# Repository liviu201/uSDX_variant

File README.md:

For information about configuring KiCad for this project, go to [Configuring_KiCad.md](./Configuring_KiCad.md)

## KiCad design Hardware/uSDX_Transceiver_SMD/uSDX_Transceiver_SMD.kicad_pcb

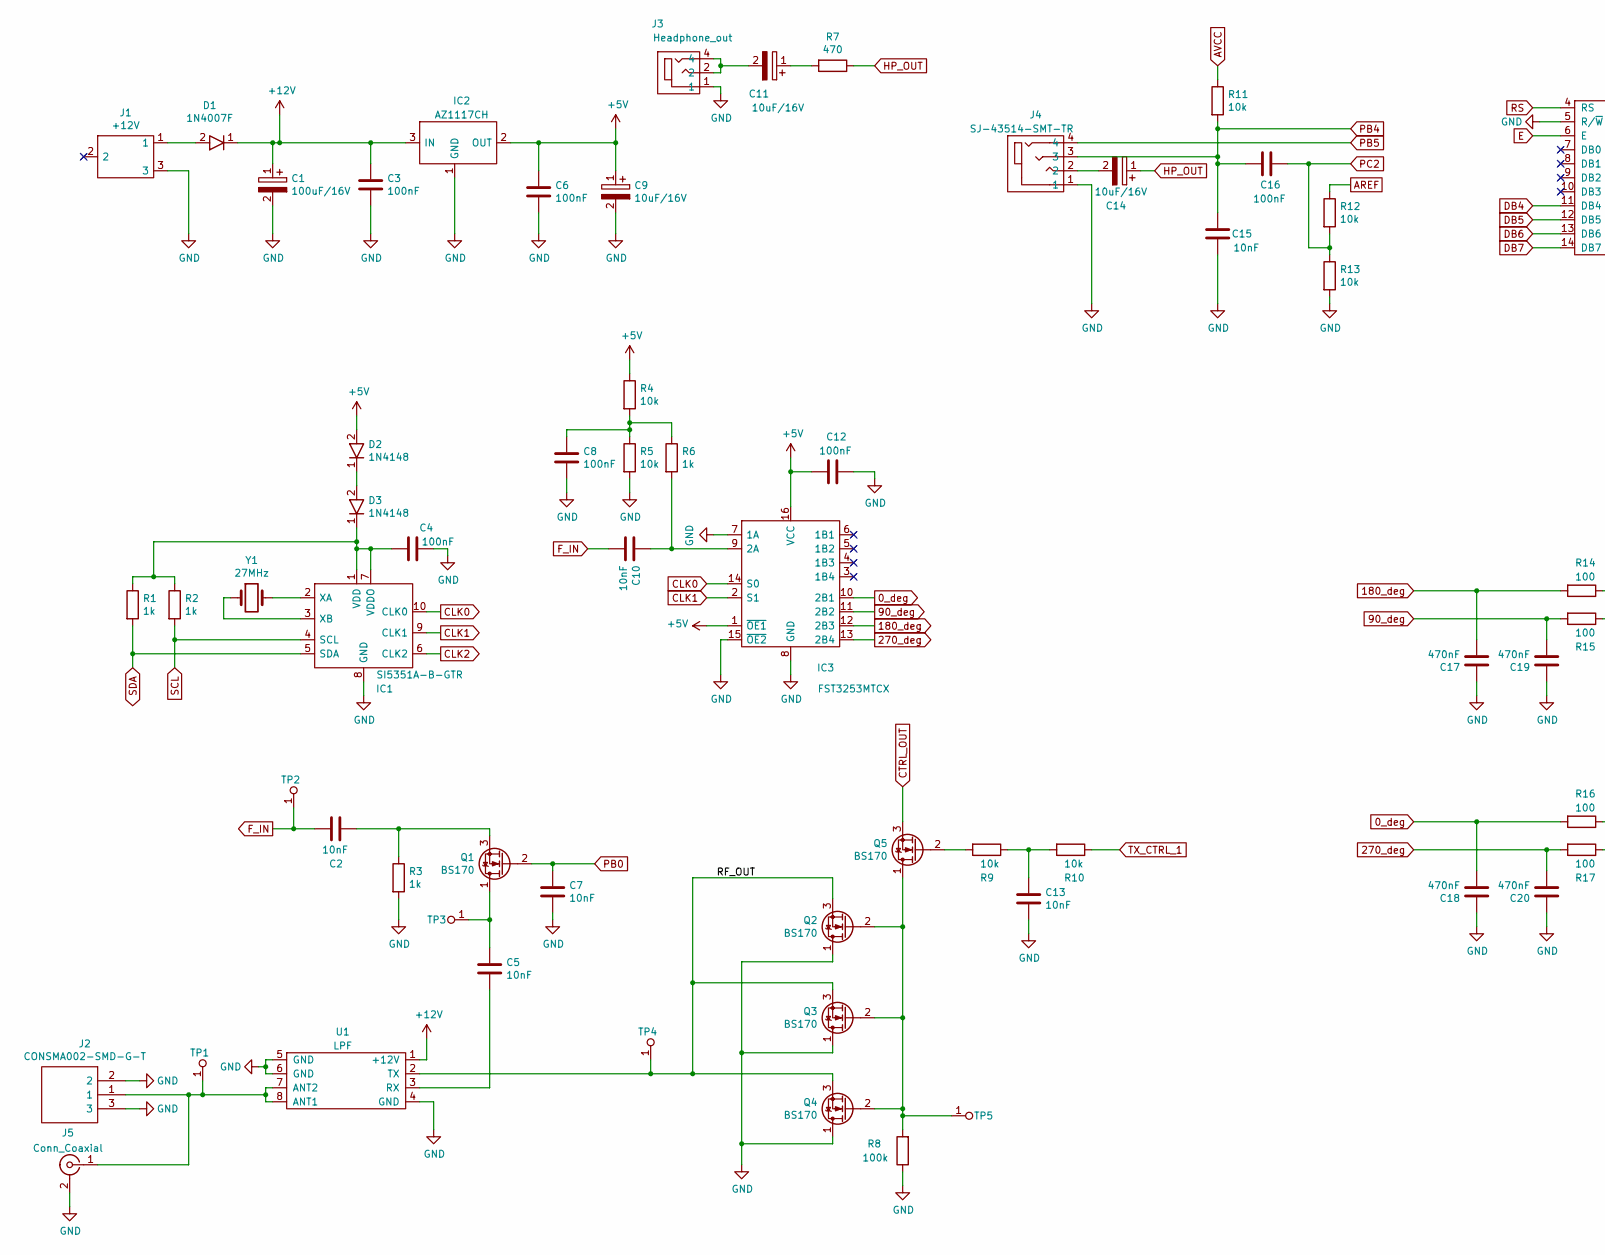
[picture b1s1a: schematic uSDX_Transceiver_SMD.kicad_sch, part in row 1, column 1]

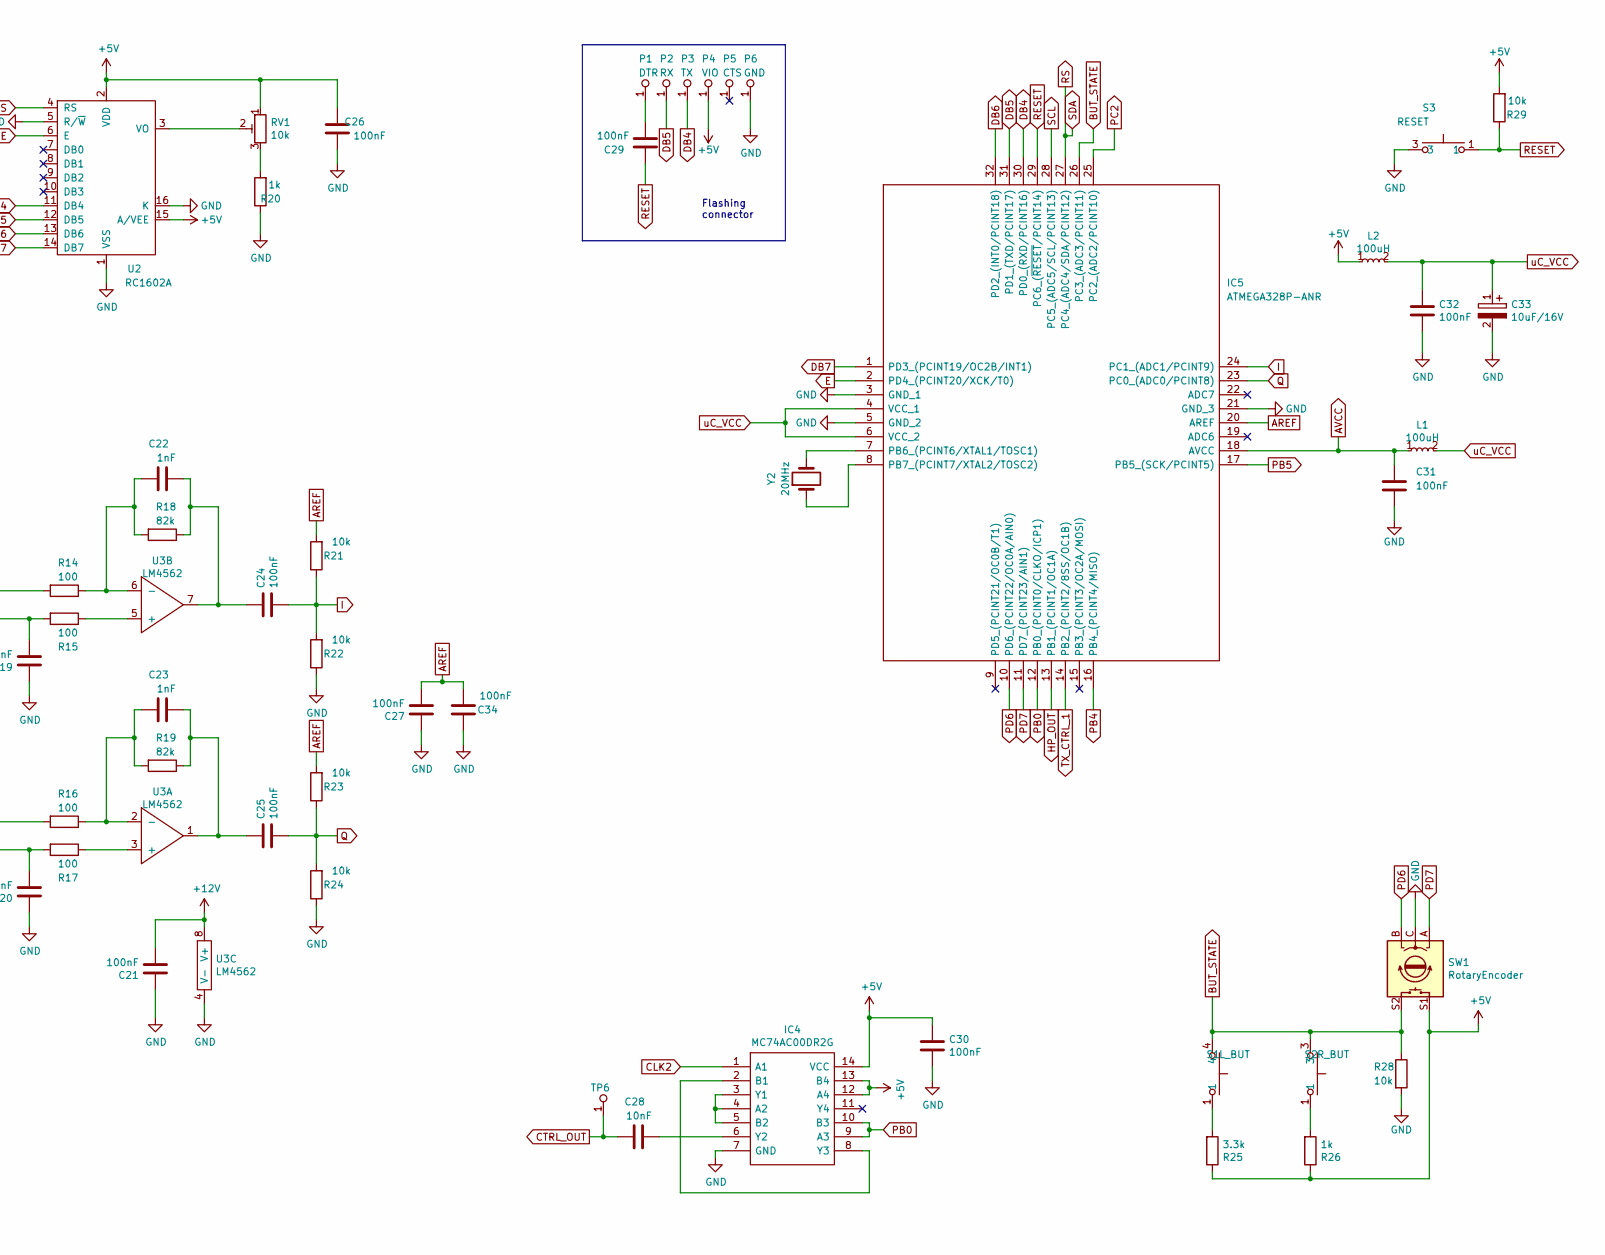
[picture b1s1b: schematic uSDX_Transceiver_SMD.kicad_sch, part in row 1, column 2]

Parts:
C1: 100uF/16V; EEE0GA101SR; Manufacturer_Part_Number EEE-FK1C101SR; Mouser Part Number 667-EEE-FK1C101SR
C2, C5, C7, C10, C13, C15, C28: 10nF; C_0805_2012Metric
C3, C4, C6, C8, C12, C16, C21, C24, C25, C26, C27, C29, C30, C31, C32, C34: 100nF; C_0805_2012Metric
C9, C11, C14, C33: 10uF/16V; CAPAE430X470N; Manufacturer_Part_Number UCQ1C100MCL1GB; Mouser Part Number 647-UCQ1C100MCL1GB
C17, C18, C19, C20: 470nF; C_0805_2012Metric
C22, C23: 1nF; C_0805_2012Metric
D1: 1N4007F; SODFL4626X110N; Manufacturer_Part_Number 1N4007F
D2, D3: 1N4148; SOD3816X135N; Manufacturer_Part_Number 1N4148W_R2_00001; Mouser Part Number 241-1N4148W_R2_00001
IC1: SI5351A-B-GTR; SOP50P490X110-10N; Manufacturer_Part_Number SI5351A-B-GTR; Mouser Part Number 634-SI5351A-B-GTR
IC2: AZ1117CH; SOT230P700X180-4N; Manufacturer_Part_Number LM1117MPX-50NOPB; Mouser Part Number 863-LM1117MPX-50NOPB
IC3: FST3253MTCX; SOP65P640X110-16N; Manufacturer_Part_Number FST3253MTCX; Mouser Part Number 512-FST3253MTCX
IC4: MC74AC00DR2G; SOIC127P600X175-14N; Manufacturer_Part_Number MC74AC00DR2G; Mouser Part Number 863-MC74AC00DR2G
IC5: ATMEGA328P-ANR; QFP80P900X900X120-32N; Manufacturer_Part_Number ATMEGA328P-ANR; Mouser Part Number 556-ATMEGA328P-ANR
J1: +12V; RASM722BKZ; Manufacturer_Part_Number 16PJ200
J2: CONSMA002-SMD-G-T; CONSMA002SMDGT; Manufacturer_Part_Number CONSMA002-SMD-G-T; Mouser Part Number 712-CONSMA002-SMD-GT
J3: Headphone_out; STX31503C1; Manufacturer_Part_Number STX-3150-3C-1; Mouser Part Number 806-STX-3150-3C-1
J4: SJ-43514-SMT-TR; SJ43514SMTTR; Manufacturer_Part_Number SJ-43514-SMT-TR; Mouser Part Number 490-SJ-43514-SMT-TR
J5: Conn_Coaxial; BNC_1-1634613-0
L1: 100uH; VLS3010CX-101M-1
L2: 100uH; MSS6122-104MLC
P1: DTR; pin_angled
P2: RX; pin_angled
P3: TX; pin_angled
P4: VIO; pin_angled
P5: CTS; pin_angled
P6: GND; pin_angled
Q1, Q2, Q3, Q4, Q5: BS170; TO-92
R1, R2, R3, R6, R20, R26: 1k; R_0805_2012Metric
R4, R5, R9, R10, R11, R12, R13, R21, R22, R23, R24, R28, R29: 10k; R_0805_2012Metric
R7: 470; R_0805_2012Metric
R8: 100k; R_0805_2012Metric
R14, R15, R16, R17: 100; R_0805_2012Metric
R18, R19: 82k; R_0805_2012Metric
R25: 3.3k; R_0805_2012Metric
RV1: 10k; Potentiometer_Vishay_TS53YJ_Vertical
S1: L_BUT; PTS125SM122LFS; Manufacturer_Part_Number PTS125SM122LFS; Mouser Part Number 611-PTS125SM12LFS
S2: R_BUT; PTS125SM122LFS; Manufacturer_Part_Number PTS125SM122LFS; Mouser Part Number 611-PTS125SM12LFS
S3: RESET; pushbutton; Manufacturer_Part_Number PTS125SM122LFS; Mouser Part Number 611-PTS125SM12LFS
SW1: RotaryEncoder; PEC11H-4220F-S0024
TP1, TP2, TP3, TP4, TP5, TP6: testpoint
U1: LPF; BPF_board
U2: RC1602A; RC1602BBIWESX
U3: LM4562; SOIC127P600X175-8N
Y1: 27MHz; XRCGB27M000F2P01R0
Y2: 20MHz; 830108207209

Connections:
0_deg: C18.2, IC3.10 (2B1), R16.2
90_deg: C19.2, IC3.11 (2B2), R15.2
180_deg: C17.2, IC3.12 (2B3), R14.2
270_deg: C20.2, IC3.13 (2B4), R17.2
+5V: C6.1, C9.1, C12.2, C26.2, C30.1, D2.2, IC2.2 (OUT), IC3.1 (~OE1), IC3.16 (VCC), IC4.12 (A4), IC4.13 (B4), IC4.14 (VCC), L2.1, P4.1, R4.1, R25.1, R26.1, R29.2, RV1.1, SW1.S1, U2.2 (VDD), U2.15 (A/VEE)
+12V: C1.1, C3.1, C21.2, D1.1, IC2.3 (IN), U1.1 (+12V), U3.8 (V+)
/RF_OUT: Q2.3 (S), Q3.3 (S), Q4.3 (S), TP4.1, U1.2 (TX)
AREF: C27.2, C34.2, IC5.20 (AREF), R12.1, R21.2, R23.2
AVCC: C31.1, IC5.18 (AVCC), L1.1, R11.1
BUT_STATE: IC5.26 (PC3_(ADC3/PCINT11)), R28.1, S1.4, S2.3, SW1.S2
CLK0: IC1.10 (CLK0), IC3.14 (S0)
CLK1: IC1.9 (CLK1), IC3.2 (S1)
CLK2: IC1.6 (CLK2), IC4.1 (A1)
CTRL_OUT: C28.1, Q5.3 (S), TP6.1
DB4: IC5.30 (PD0_(RXD/PCINT16)), P3.1, U2.11 (DB4)
DB5: IC5.31 (PD1_(TXD/PCINT17)), P2.1, U2.12 (DB5)
DB6: IC5.32 (PD2_(INT0/PCINT18)), U2.13 (DB6)
DB7: IC5.1 (PD3_(PCINT19/OC2B/INT1)), U2.14 (DB7)
E: IC5.2 (PD4_(PCINT20/XCK/T0)), U2.6 (E)
F_IN: C2.2, C10.2, TP2.1
GND: C1.2, C3.2, C4.2, C6.2, C7.2, C8.2, C9.2, C12.1, C13.2, C15.1, C17.1, C18.1, C19.1, C20.1, C21.1, C26.1, C27.1, C30.2, C31.2, C32.2, C33.2, C34.1, IC1.8 (GND), IC2.1 (GND), IC3.7 (1A), IC3.8 (GND), IC3.15 (~OE2), IC4.7 (GND), IC5.3 (GND_1), IC5.5 (GND_2), IC5.21 (GND_3), J1.3, J2.2, J2.3, J3.1, J4.1, J5.2 (Ext), P6.1, Q2.1 (D), Q3.1 (D), Q4.1 (D), R3.2, R5.2, R8.1, R13.2, R20.1, R22.1, R24.1, R28.2, S3.3, SW1.C, U1.4 (GND), U1.5 (GND), U1.6 (GND), U2.1 (VSS), U2.5 (R/~W), U2.16 (K), U3.4 (V-)
HP_OUT: C14.1, IC5.13 (PB1_(PCINT1/OC1A)), R7.1
I: C24.2, IC5.24 (PC1_(ADC1/PCINT9)), R21.1, R22.2
unnamed: C2.1, Q1.3 (S), R3.1
unnamed: C4.1, D3.1, IC1.1 (VDD), IC1.7 (VDDO), R1.1, R2.1
unnamed: C5.1, Q1.1 (D), TP3.1
unnamed: C5.2, U1.3 (RX)
unnamed: C8.1, R4.2, R5.1, R6.1
unnamed: C10.1, IC3.9 (2A), R6.2
unnamed: C11.1, R7.2
unnamed: C11.2, J3.2, J3.4
unnamed: C13.1, R9.1, R10.2
unnamed: C14.2, J4.2
unnamed: C22.1, R14.1, R18.2, U3.6 (-)
unnamed: C22.2, C24.1, R18.1, U3.7
unnamed: C23.1, R16.1, R19.2, U3.2 (-)
unnamed: C23.2, C25.1, R19.1, U3.1
unnamed: C28.2, IC4.6 (Y2)
unnamed: C29.1, P1.1
unnamed: D1.2, J1.1
unnamed: D2.1, D3.2
unnamed: IC1.2 (XA), Y1.3
unnamed: IC1.3 (XB), Y1.1
unnamed: IC4.2 (B1), IC4.8 (Y3)
unnamed: IC4.3 (Y1), IC4.4 (A2), IC4.5 (B2)
unnamed: IC5.7 (PB6_(PCINT6/XTAL1/TOSC1)), Y2.3
unnamed: IC5.8 (PB7_(PCINT7/XTAL2/TOSC2)), Y2.1
unnamed: J2.1, J5.1 (In), TP1.1, U1.7 (ANT2), U1.8 (ANT1)
unnamed: Q2.2 (G), Q3.2 (G), Q4.2 (G), Q5.1 (D), R8.2, TP5.1
unnamed: Q5.2 (G), R9.2
unnamed: R15.1, U3.5 (+)
unnamed: R17.1, U3.3 (+)
unnamed: R20.2, RV1.3
unnamed: R25.2, S1.1
unnamed: R26.2, S2.1
unnamed: RV1.2, U2.3 (VO)
PB0: C7.1, IC4.9 (A3), IC4.10 (B3), IC5.12 (PB0_(PCINT0/CLKO/ICP1)), Q1.2 (G)
PB4: C15.2, C16.2, IC5.16 (PB4_(PCINT4/MISO)), J4.3, R11.2
PB5: IC5.17 (PB5_(SCK/PCINT5)), J4.4
PC2: C16.1, IC5.25 (PC2_(ADC2/PCINT10)), R12.2, R13.1
PD6: IC5.10 (PD6_(PCINT22/OC0A/AIN0)), SW1.B
PD7: IC5.11 (PD7_(PCINT23/AIN1)), SW1.A
Q: C25.2, IC5.23 (PC0_(ADC0/PCINT8)), R23.1, R24.2
RESET: C29.2, IC5.29 (PC6_(~RESET/PCINT14)), R29.1, S3.1
RS: IC1.5 (SDA), IC5.27 (PC4_(ADC4/SDA/PCINT12)), R1.2, U2.4 (RS)
SCL: IC1.4 (SCL), IC5.28 (PC5_(ADC5/SCL/PCINT13)), R2.2
TX_CTRL_1: IC5.14 (PB2_(PCINT2/8SS/OC1B)), R10.1
uC_VCC: C32.1, C33.1, IC5.4 (VCC_1), IC5.6 (VCC_2), L1.2, L2.2

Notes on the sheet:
Flashing connector

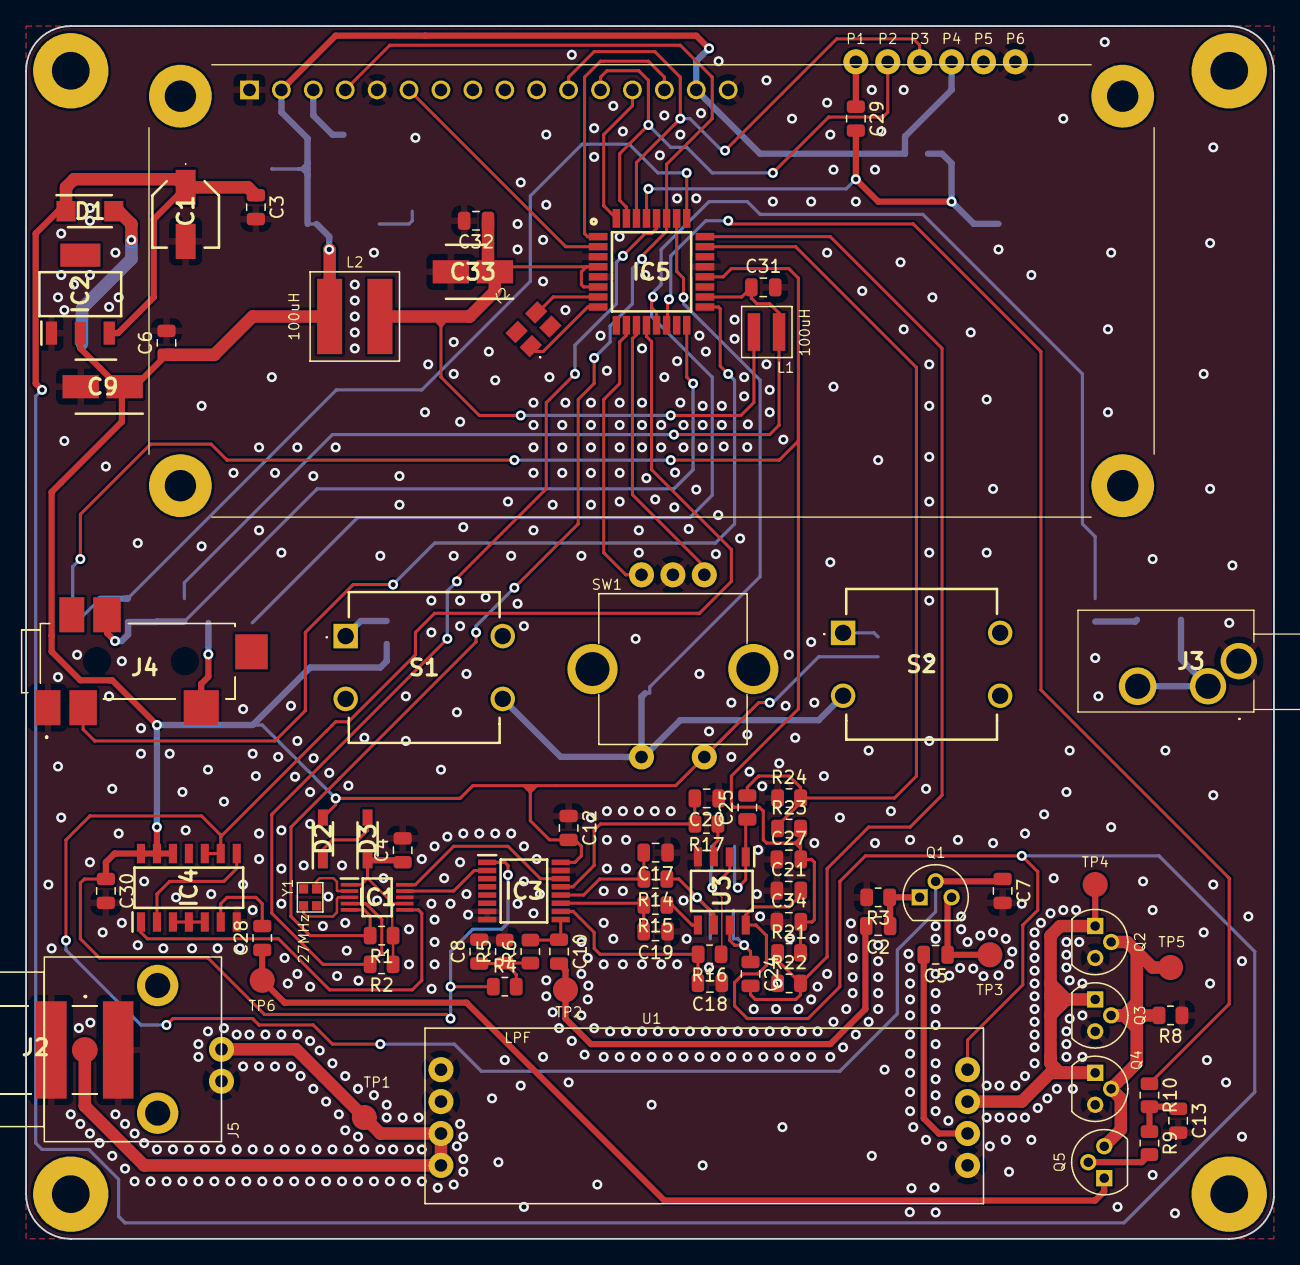
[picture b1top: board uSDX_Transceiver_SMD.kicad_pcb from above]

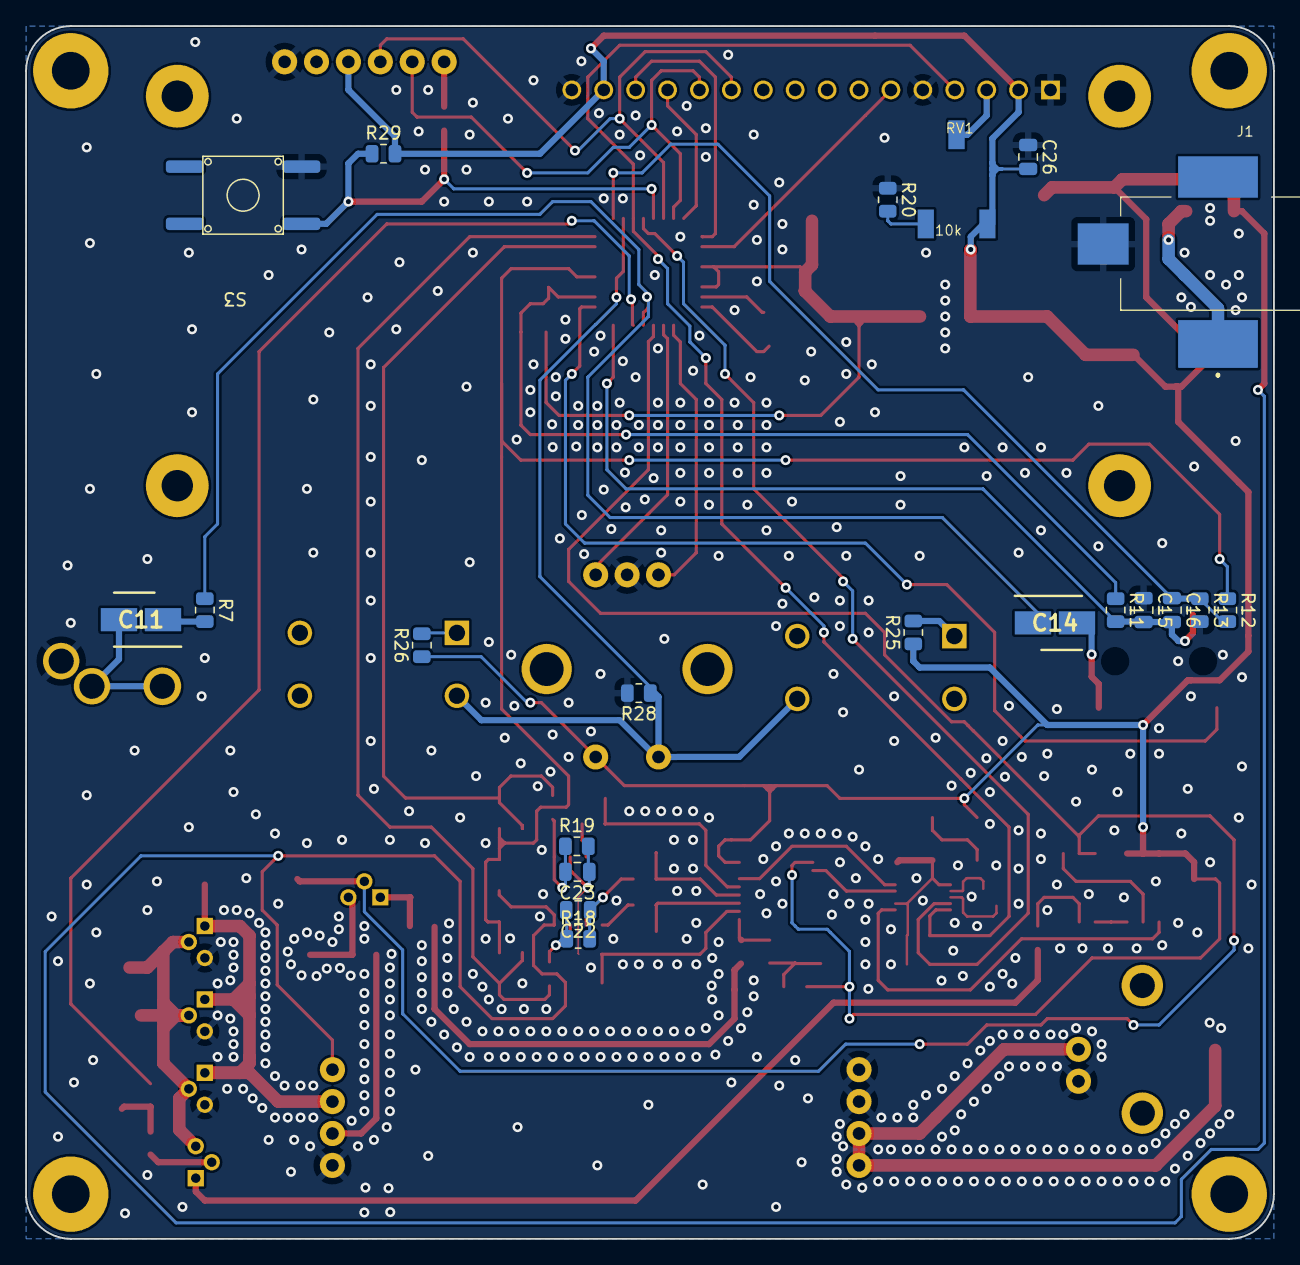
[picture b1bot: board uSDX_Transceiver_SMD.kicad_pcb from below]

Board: 2 copper layers, 99.3 x 96.5 mm, 108 parts (21 on the bottom side), 68 nets.

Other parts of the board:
 : MountingHole_3mm_Pad
 #2,  #3,  #4: MountingHole_3mm_Pad

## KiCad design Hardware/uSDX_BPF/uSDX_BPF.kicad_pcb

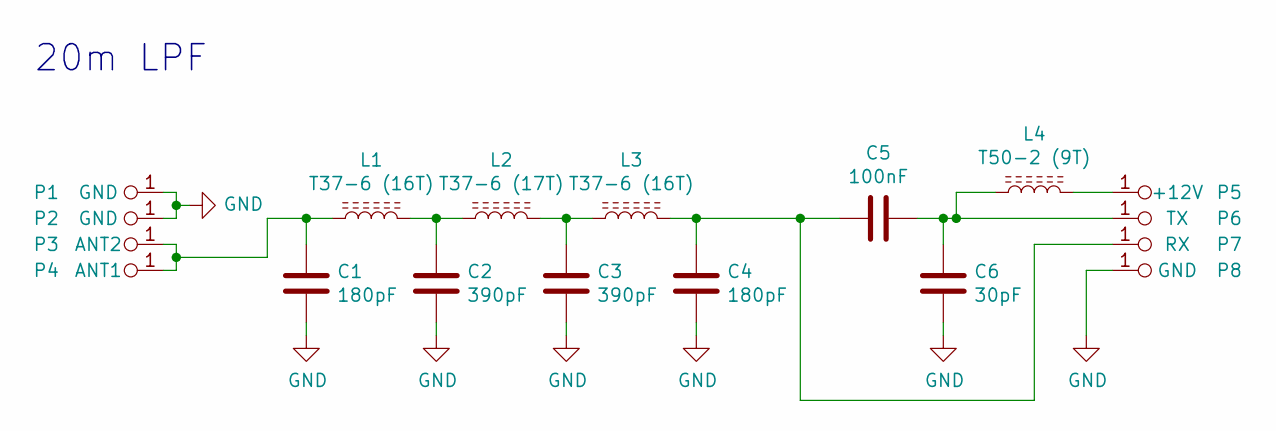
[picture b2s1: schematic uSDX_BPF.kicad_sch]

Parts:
C1, C4: 180pF; C_Disc_D3.0mm_W1.6mm_P2.50mm
C2, C3: 390pF; C_Disc_D3.0mm_W1.6mm_P2.50mm
C5: 100nF; C_Disc_D3.0mm_W1.6mm_P2.50mm
C6: 30pF; C_Disc_D3.0mm_W1.6mm_P2.50mm
L1, L3: T37-6 (16T); L_Toroid_Vertical_L10.0mm_W5.0mm_P5.08mm
L2: T37-6 (17T); L_Toroid_Vertical_L10.0mm_W5.0mm_P5.08mm
L4: T50-2 (9T); L_Toroid_Vertical_L10.0mm_W5.0mm_P5.08mm
P1, P2, P8: GND; pin
P3: ANT2; pin
P4: ANT1; pin
P5: +12V; pin
P6: TX; pin
P7: RX; pin

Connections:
GND: C1.2, C2.2, C3.2, C4.2, C6.2, P1.1, P2.1, P8.1
unnamed: C1.1, L1.1, P3.1, P4.1
unnamed: C2.1, L1.2, L2.1
unnamed: C3.1, L2.2, L3.1
unnamed: C4.1, C5.2, L3.2, P7.1
unnamed: C5.1, C6.1, L4.1, P6.1
unnamed: L4.2, P5.1

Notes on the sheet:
20m LPF

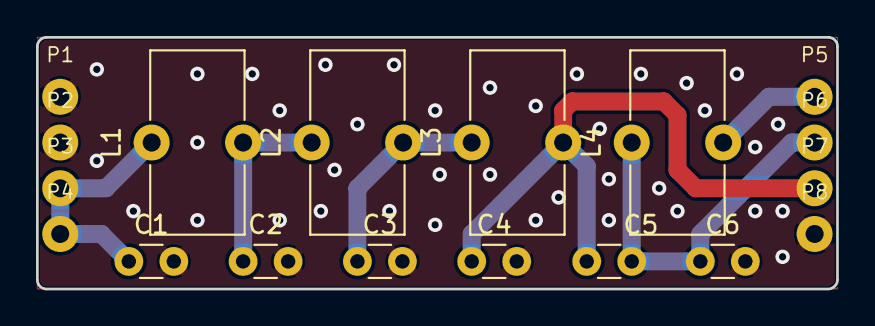
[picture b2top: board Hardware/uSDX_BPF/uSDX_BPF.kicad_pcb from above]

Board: 2 copper layers, 44.5 x 14.0 mm, 18 parts (0 on the bottom side), 7 nets.

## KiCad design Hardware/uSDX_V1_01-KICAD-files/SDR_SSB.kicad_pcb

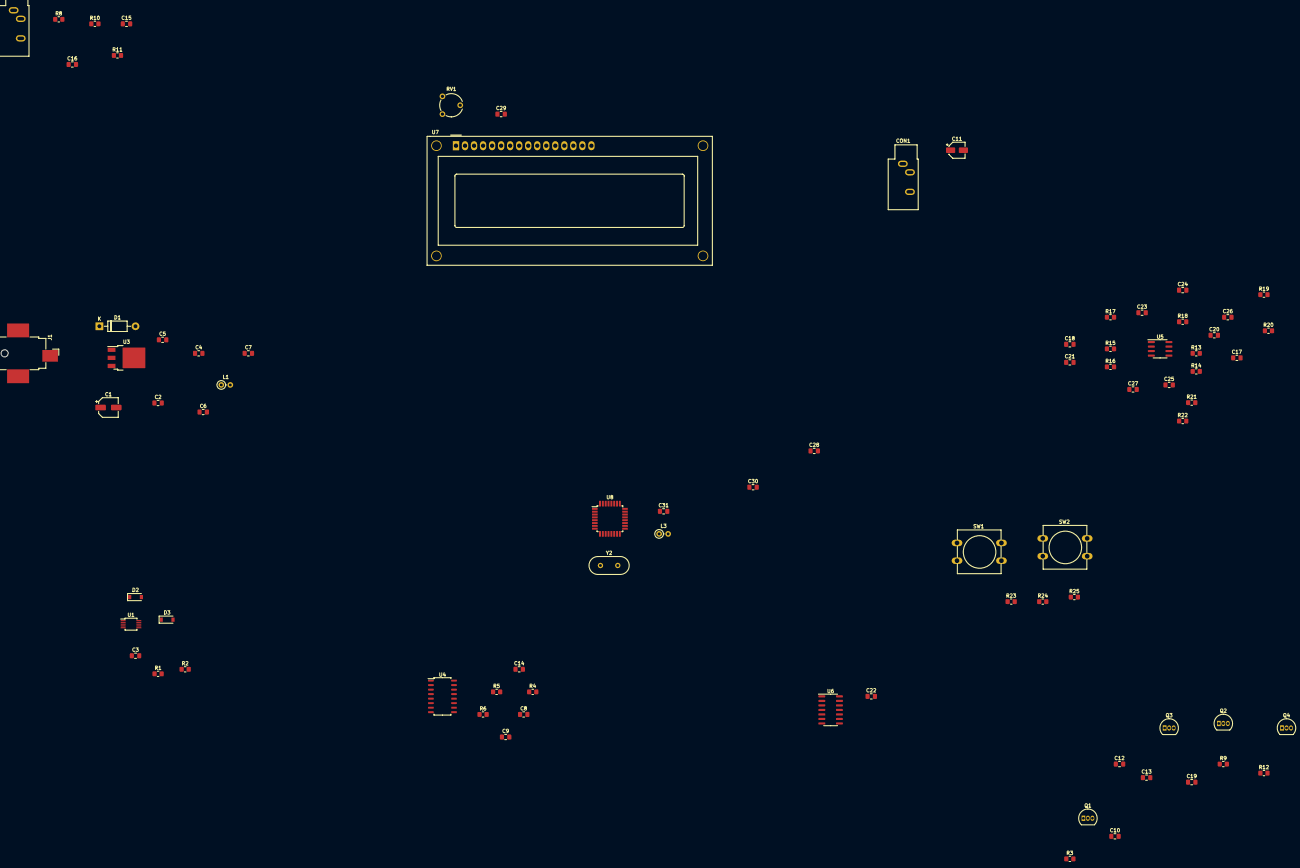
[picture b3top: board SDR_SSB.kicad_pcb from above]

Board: 2 copper layers, 79 parts (1 on the bottom side), 53 nets, no tracks yet.

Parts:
C1: 100u/16V; CP_Elec_5x5.8
C2, C3, C4, C6, C8, C12, C14, C16, C22, C25, C26, C27, C28, C29, C31: 100nF; C_0805_2012Metric_Pad1.18x1.45mm_HandSolder
C5, C7: 10uF; C_0805_2012Metric_Pad1.18x1.45mm_HandSolder
C9, C10, C15, C19, C30: 10nF; C_0805_2012Metric_Pad1.18x1.45mm_HandSolder
C11: 10uF/16V; CP_Elec_4x4.5
C13: 33pF; C_0805_2012Metric_Pad1.18x1.45mm_HandSolder
C17, C18, C20, C21: 470nF; C_0805_2012Metric_Pad1.18x1.45mm_HandSolder
C23, C24: 1nF; C_0805_2012Metric_Pad1.18x1.45mm_HandSolder
CON1: HEADPHONE; Jack_3.5mm_CUI_SJ1-3533NG_Horizontal
CON2: MIC/PTT; Jack_3.5mm_CUI_SJ1-3533NG_Horizontal
D1: 1N4007; D_DO-41_SOD81_P10.16mm_Horizontal
D2, D3: 1N4148W; D_SOD-123
J1: DC 12V; BarrelJack_CUI_PJ-036AH-SMT_Horizontal
L1, L3: 100uH; L_Axial_L5.3mm_D2.2mm_P2.54mm_Vertical_Vishay_IM-1
Q1, Q2, Q3, Q4: BS170; TO-92_Inline
R1, R2, R3, R6, R24: 1k; R_0805_2012Metric_Pad1.20x1.40mm_HandSolder
R4, R5, R8, R9, R10, R11, R12, R19, R20, R21, R22, R25: 10k; R_0805_2012Metric_Pad1.20x1.40mm_HandSolder
R7: 470; R_0805_2012Metric_Pad1.20x1.40mm_HandSolder
R13, R14, R15, R16: 100; R_0805_2012Metric_Pad1.20x1.40mm_HandSolder
R17, R18: 82k; R_0805_2012Metric_Pad1.20x1.40mm_HandSolder
R23: 3.3k; R_0805_2012Metric_Pad1.20x1.40mm_HandSolder
RV1: 10k; Potentiometer_Piher_PT-6-V_Vertical
SW1: L_Button; SW_PUSH-12mm
SW2: R_Button; SW_PUSH-12mm
U1: Si5351A-B-GT; MSOP-10_3x3mm_P0.5mm
U3: L7805CV; TO-252-3_TabPin4
U4: FST3253; SOIC-16_4.55x10.3mm_P1.27mm
U5: LM4562; SOIC-8_3.9x4.9mm_P1.27mm
U6: 74ACT00; SOIC-14_3.9x8.7mm_P1.27mm
U7: RC1602A; WC1602A
U8: ATMEGA328-PU; TQFP-32_7x7mm_P0.8mm
Y2: 20 Mhz; Crystal_HC49-U_Vertical

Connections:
0_deg: C18.1, R15.1, U4.10
90_deg: C17.2, R14.1, U4.11
180_deg: C20.2, R13.1, U4.12
270_deg: C21.1, R16.1, U4.13
+5V: C6.1, C7.1, C14.1, C22.1, C29.1, D2.2, L1.2, L3.1, R4.1, R23.2, R24.2, RV1.1, U4.1, U4.16, U6.12, U6.13, U6.14, U7.2, U7.15, U8.7
+12V: C1.1, C2.1, C25.1, D1.2, U3.1, U5.8
AREF: C28.2, R10.1, R19.2, R21.2, U8.21
AVCC: C31.1, L3.2, R8.1, U8.20
BUT_STATE: R25.1, SW1.1, SW2.1, U8.26
CLK_0: U1.10, U4.14
CLK_1: U1.9, U4.2
CLK_2: U1.6, U6.1
CTRL_OUT: C30.1, Q2.2, Q3.2, Q4.2, R9.2
DB4: U7.11, U8.2
DB5: U7.12, U8.3
DB6: U7.13, U8.4
DB7: U7.14, U8.5
E: U7.6, U8.6
F_IN: C9.2, Q1.3, R3.1
GNDPWR: C1.2, C2.2, C3.1, C4.2, C5.2, C6.2, C7.2, C8.2, C10.1, C13.2, C14.2, C15.2, C17.1, C18.2, C19.2, C20.1, C21.2, C22.2, C25.2, C28.1, C29.2, C31.2, J1.2, Q2.3, Q3.3, Q4.3, R3.2, R5.2, R11.2, R20.1, R22.1, R25.2, RV1.3, U1.8, U3.2, U4.7, U4.8, U4.15, U5.4, U6.7, U7.1, U7.5, U7.16, U8.8, U8.22
HP_OUT: R7.1, U8.15
I: C26.2, R19.1, R20.2, U8.23
unnamed: C3.2, D3.1, R1.1, R2.1, U1.1, U1.7
unnamed: C4.1, C5.1, L1.1, U3.3
unnamed: C8.1, R4.2, R5.1, R6.1
unnamed: C9.1, R6.2, U4.9
unnamed: C11.1, R7.2
unnamed: C12.1, C13.1, Q2.1, Q3.1, Q4.1
unnamed: C19.1, R9.1, R12.2
unnamed: C23.1, R15.2, R17.1, U5.2
unnamed: C23.2, C27.1, R17.2, U5.1
unnamed: C24.1, R13.2, R18.1, U5.6
unnamed: C24.2, C26.1, R18.2, U5.7
unnamed: C30.2, U6.6
unnamed: D1.1, J1.1
unnamed: D2.1, D3.2
unnamed: R14.2, U5.5
unnamed: R16.2, U5.3
unnamed: R23.1, SW1.2
unnamed: R24.1, SW2.2
unnamed: RV1.2, U7.3
unnamed: U6.2, U6.8
unnamed: U6.3, U6.4, U6.5
unnamed: U8.9, Y2.1
unnamed: U8.10, Y2.2
PB0: C10.2, Q1.2, U6.9, U6.10, U8.14
PB4: C15.1, C16.1, R8.2, U8.18
PC2: C16.2, R10.2, R11.1, U8.25
Q: C27.2, R21.1, R22.2, U8.24
RF_SIGNAL: C12.2, Q1.1
RS: R1.2, U1.5, U7.4, U8.27
SCL: R2.2, U1.4, U8.28
TX_CTRL_1: R12.1, U8.16

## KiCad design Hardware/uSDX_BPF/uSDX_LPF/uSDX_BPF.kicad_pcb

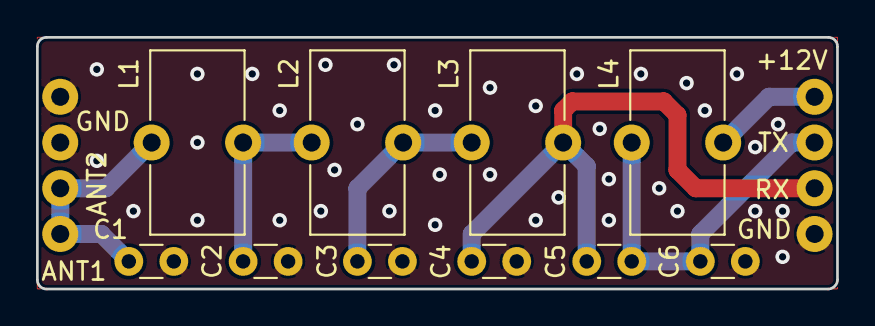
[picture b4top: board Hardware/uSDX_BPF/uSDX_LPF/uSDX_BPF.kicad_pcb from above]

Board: 2 copper layers, 44.5 x 14.0 mm, 18 parts (0 on the bottom side), 7 nets.

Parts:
 : pin
+12V: pin
ANT1, ANT2: pin
C1: 180pF; C_Disc_D3.0mm_W1.6mm_P2.50mm
C2: 390pF; C_Disc_D3.0mm_W1.6mm_P2.50mm
C3, C4, C5, C6: C_Disc_D3.0mm_W1.6mm_P2.50mm
GND: pin
GND#2: pin
L1, L3: T37-6 (16T); L_Toroid_Vertical_L10.0mm_W5.0mm_P5.08mm
L2: T37-6 (17T); L_Toroid_Vertical_L10.0mm_W5.0mm_P5.08mm
L4: L_Toroid_Vertical_L10.0mm_W5.0mm_P5.08mm
RX: pin
TX: TX; pin

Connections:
GND: .1, C1.2, C2.2, C3.2, C4.2, C6.2, GND.1, GND#2.1
unnamed: ANT1.1, ANT2.1, C1.1, L1.1
unnamed: C2.1, L1.2, L2.1
unnamed: C3.1, L2.2, L3.1
unnamed: C4.1, C5.2, L3.2, RX.1
unnamed: C5.1, C6.1, L4.1, TX.1
unnamed: +12V.1, L4.2

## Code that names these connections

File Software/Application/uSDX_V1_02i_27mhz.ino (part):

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#define LCD_D7  3         //PD3    (pin 5)
#define LCD_EN  4         //PD4    (pin 6)
#define FREQCNT 5         //PD5    (pin 11)
#define ROT_A   7         //PD6    (pin 12) //was 6
#define ROT_B   6         //PD7    (pin 13) //was 7
#define RX      8         //PB0    (pin 14)
#define SIDETONE 9        //PB1    (pin 15)
#define KEY_OUT 10        //PB2    (pin 16)
#define SIG_OUT 11        //PB3    (pin 17)
#define DAH     12        //PB4    (pin 18)
#define DIT     13        //PB5    (pin 19)
#define AUDIO1  14        //PC0/A0 (pin 23)
#define AUDIO2  15        //PC1/A1 (pin 24)
#define DVM     16        //PC2/A2 (pin 25)
#define BUTTONS 17        //PC3/A3 (pin 26)
#define LCD_RS  18        //PC4    (pin 27)
#define SDA     18        //PC4    (pin 27)
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    SendRegister(26+pll*8, pll_regs, 8); // Write to PLL[pll]
  }

  void set_ms(uint8_t clk, uint8_t linked_pll, uint8_t msa, uint8_t rdiv, uint8_t phase){  // Set Multisynth divider (integer) CLK0=0, CLK1=1, CLK2=2
    uint32_t msp1 = (128*msa - 512) | (((uint32_t)rdiv)<<20);     // msp1 and msp2=0, msp3=1, not fractional
    uint8_t ms_regs[8] = {0, 1, BB2(msp1), BB1(msp1), BB0(msp1), 0, 0, 0};
    SendRegister(42+clk*8, ms_regs, 8); // Write to MS[clk]
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
  void pll_reset(){ if(dirty){ dirty=false; SendRegister(177, 0xA0); } } // reset PLLA and PLLB, if necessary

  void oe(uint8_t mask){ SendRegister(3, ~mask); } // Output-enable mask: CLK2=4; CLK1=2; CLK0=1

  void freq(uint32_t f, uint8_t i, uint8_t q){  // Set CLK0,1 (PLLA) to fout Hz with phase i, q, and prepare CLK2 (PLL2).
    set_freq(0, 0, f, i);
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
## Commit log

2021-07-26 initial commit - HW schematic improved
2021-09-25 updated component footprints
2021-10-12 updated HW design
2021-12-31 updated the HW design
2022-01-01 completed the HW design
2022-01-09 updated the hardware design
2022-01-12 modified the HW design, corrected mistakes
2022-01-13 updated the HW desigin and 3D models
2022-01-15 updated the 3D models
2022-01-15 updated the project with transferrable libraries
2022-01-16 update library locations
2022-01-16 added description for configuring the paths
2022-01-16 Update README.md
    updated the broken image path
2022-01-16 removed unnecessary libraries
2022-01-16 updated .gitignore
2022-01-16 updated md files
2022-01-20 updated the documentation
2022-01-30 added CMake project and lcd driver
2022-01-30 added tools
2022-02-15 fixed CMake configuration, added test code for the lcd driver
2022-07-17 Fixed CMake configuration for unit tests
2022-07-19 added tests for the LCD

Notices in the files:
Software/Application/uSDX_V1_02i_27mhz.ino:
Copyright 2019, 2020 Guido PE1NNZ <pe1nnz@amsat.org>
